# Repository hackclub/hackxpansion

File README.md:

<h1 align="center">
    Hackxpansion
</h1>

<h3 align="center">
    <a href="https://hackxpansion.koeg.dev">Website</a>
    <br/>
</h3>

<h4 align="center">
    A handheld console with 4 expansion solts
</h4>

<div align="center">
    
</div>

## Key Features

- Resistor based module identification at start up
- [2" 240x320 ST7789 LCD panel](https://www.buydisplay.com/2-inch-ips-tft-lcd-display-ips-panel-screen-240x320-for-smart-watch)
- RP2354 MCU
- Easily adaptable [module standard](https://hackxpansion.dino.icu/docs/detailed/card)
- Rust firmware with [embassy](https://embassy.dev/) and [slint-ui](https://slint.dev/)

## Why?

I really like the idea of modules, and modular things, and making people work together, so I made this.

## PCB

The console has two 4 layer PCBs designed in KiCAD, a main-board and a daughter-board, designed for JLC's basic process. 

### Main-Board

### Daughter-Board

## Making Your Own Modules

There are three simple steps to making your own module:

1. Design the module PCB in KiCAD
2. Design the module case in CAD
3. Write a driver for the module

There are detailed docs on the [hackxpansion website](https://hackxpansion.dino.icu/docs)

## Case

The case is designed in Autodesk Fusion, there are .f3z files in the hardware directory.

The models have parameters that can be adjusted to fit your needs.

## Shoutouts

Thank you so much for [Simon](https://github.com/NEOgHacking) who helped with the fanout of the RP, and also gave a ton of constructive feedback!!!!

## Zine

## BOM for Console

This is for an order of 2 PCBA PCBs.

Also found in a [CSV file](hardware/hackxpansion/BOM.csv). Each component has an LCSC part number attached that can be used to find the component on the LCSC website.

|Item                      |Price per unit|Nr of units|Total price|Link                                                                                          |
|--------------------------|--------------|-----------|-----------|----------------------------------------------------------------------------------------------|
|PCB with PCBA             |$60.00        |1          |$60.00     |https://jlcpcb.com/                                                                           |
|Display                   |$4.36         |1          |$4.36      |https://www.buydisplay.com/2-inch-ips-tft-lcd-display-ips-panel-screen-240x320-for-smart-watch|
|2x7 2.54mm header         |$0.386        |10         |$3.860     |https://www.aliexpress.com/item/1005012166781874.html                                         |
|Battery 502035            |$6.64         |1          |$6.64      |https://www.aliexpress.com/item/1005008218024646.html                                         |
|M2 OD3 L2 heat set insert |$0.0696       |15         |$1.0440    |https://www.aliexpress.com/item/1005006798286851.html                                         |
|M2 L6 screw               |$0.0766       |5          |$0.3830    |https://www.aliexpress.com/item/4000970993800.html                                            |
|M2 L8 screw               |$0.0766       |2          |$0.1532    |https://www.aliexpress.com/item/4000970993800.html                                            |
|M2 L4 screw               |$0.0766       |8          |$0.6128    |https://www.aliexpress.com/item/4000970993800.html                                            |
|                          |              |Total:     |$77.05     |                                                                                              |

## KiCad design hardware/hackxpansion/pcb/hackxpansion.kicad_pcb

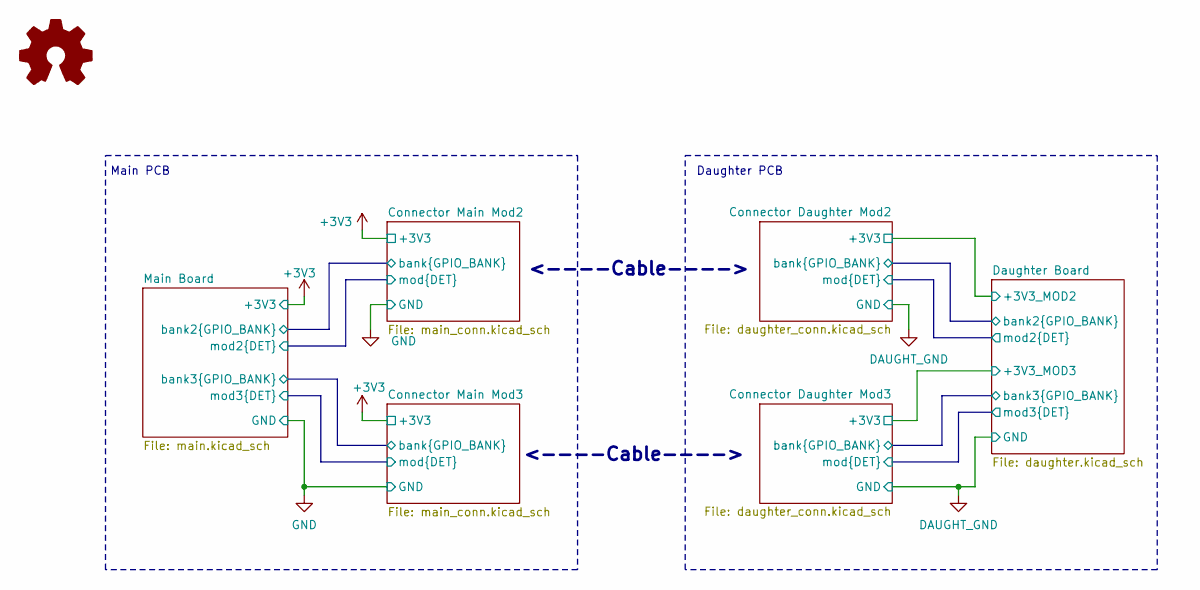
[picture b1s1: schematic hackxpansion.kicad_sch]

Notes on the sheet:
<----Cable---->
Main PCB
Daughter PCB

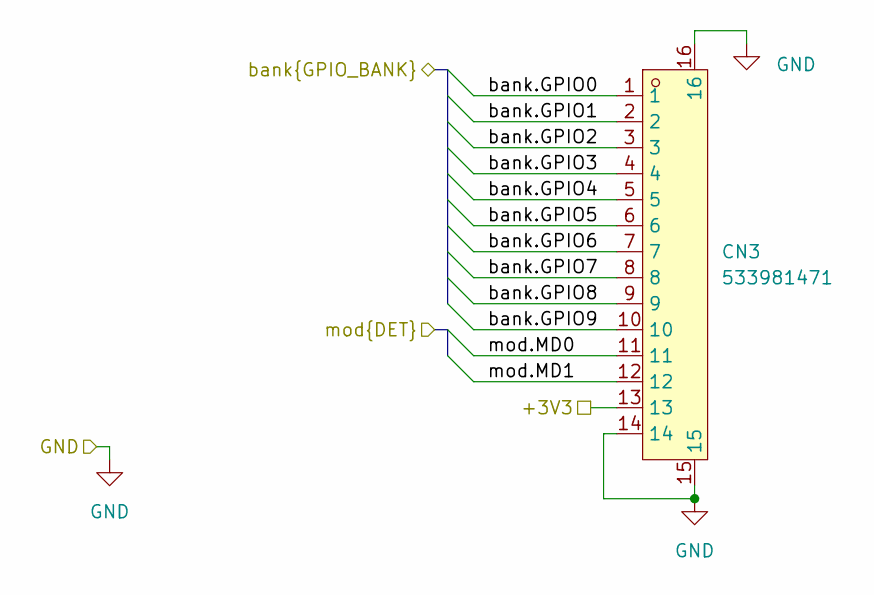
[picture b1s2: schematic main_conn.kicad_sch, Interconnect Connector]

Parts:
CN3: 533981471; CONN-SMD_14P-P1.25_MOLEX_533981471; MPN 533981471; LCSC C2886291

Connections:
/+3V3: CN3.13; also elsewhere on the board
/Connector Main Mod2/bank.GPIO0: CN3.1; also elsewhere on the board
/Connector Main Mod2/bank.GPIO1: CN3.2; also elsewhere on the board
/Connector Main Mod2/bank.GPIO2: CN3.3; also elsewhere on the board
/Connector Main Mod2/bank.GPIO3: CN3.4; also elsewhere on the board
/Connector Main Mod2/bank.GPIO4: CN3.5; also elsewhere on the board
/Connector Main Mod2/bank.GPIO5: CN3.6; also elsewhere on the board
/Connector Main Mod2/bank.GPIO6: CN3.7; also elsewhere on the board
/Connector Main Mod2/bank.GPIO7: CN3.8; also elsewhere on the board
/Connector Main Mod2/bank.GPIO8: CN3.9; also elsewhere on the board
/Connector Main Mod2/bank.GPIO9: CN3.10; also elsewhere on the board
/Connector Main Mod2/mod.MD0: CN3.11; also elsewhere on the board
/Connector Main Mod2/mod.MD1: CN3.12; also elsewhere on the board
/GND: CN3.14, CN3.15, CN3.16; also elsewhere on the board

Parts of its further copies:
CN2: 533981471; CONN-SMD_14P-P1.25_MOLEX_533981471; MPN 533981471; LCSC C2886291

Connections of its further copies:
/+3V3: CN2.13; also elsewhere on the board
/Connector Main Mod3/bank.GPIO0: CN2.1; also elsewhere on the board
/Connector Main Mod3/bank.GPIO1: CN2.2; also elsewhere on the board
/Connector Main Mod3/bank.GPIO2: CN2.3; also elsewhere on the board
/Connector Main Mod3/bank.GPIO3: CN2.4; also elsewhere on the board
/Connector Main Mod3/bank.GPIO4: CN2.5; also elsewhere on the board
/Connector Main Mod3/bank.GPIO5: CN2.6; also elsewhere on the board
/Connector Main Mod3/bank.GPIO6: CN2.7; also elsewhere on the board
/Connector Main Mod3/bank.GPIO7: CN2.8; also elsewhere on the board
/Connector Main Mod3/bank.GPIO8: CN2.9; also elsewhere on the board
/Connector Main Mod3/bank.GPIO9: CN2.10; also elsewhere on the board
/Connector Main Mod3/mod.MD0: CN2.11; also elsewhere on the board
/Connector Main Mod3/mod.MD1: CN2.12; also elsewhere on the board
/GND: CN2.14, CN2.15, CN2.16; also elsewhere on the board

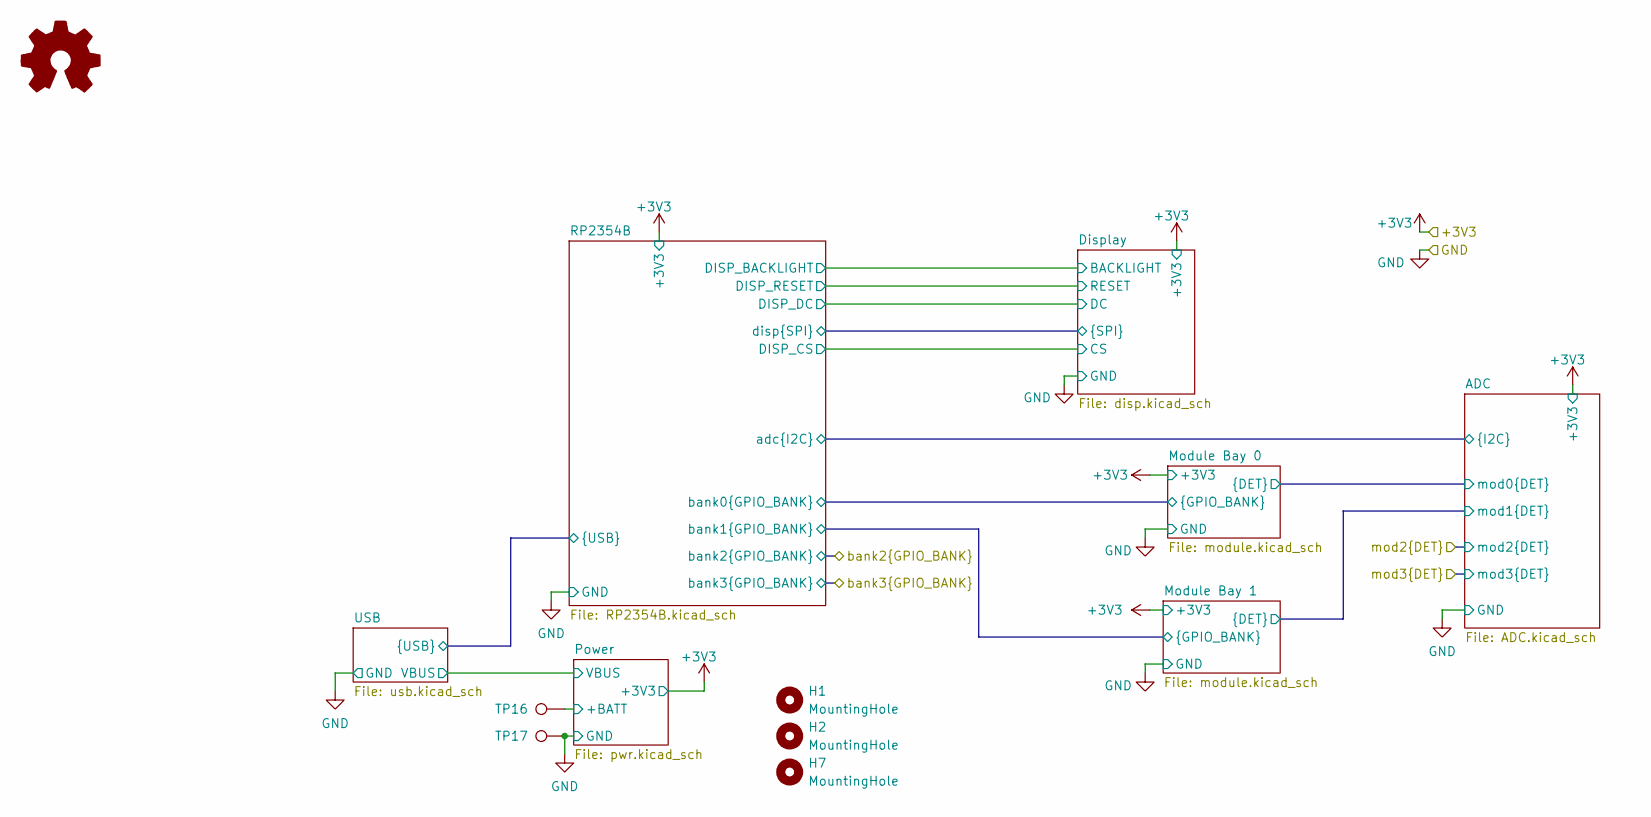
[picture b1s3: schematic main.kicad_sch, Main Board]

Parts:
H1, H2, H7: MountingHole; MountingHole_2.2mm_M2
SYM1: Logo_Open_Hardware_Small; OSHW-Logo2_14.6x12mm_SilkScreen
TP16: BATT+; TestPoint_Pad_D1.5mm
TP17: BATT-; TestPoint_Pad_D1.5mm

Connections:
/GND: TP17.1 (1_1); also elsewhere on the board
/Main Board/Power/+BATT: TP16.1 (1_1); also elsewhere on the board

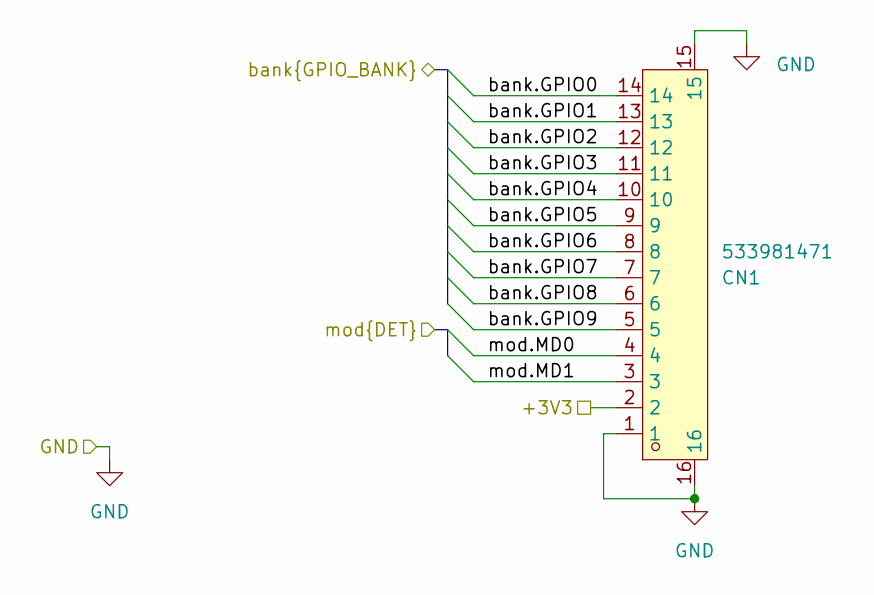
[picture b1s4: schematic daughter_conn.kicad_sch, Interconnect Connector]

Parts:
CN1: 533981471; CONN-SMD_14P-P1.25_MOLEX_533981471; MPN 533981471; LCSC C2886291

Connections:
/Connector Daughter Mod2/bank.GPIO0: CN1.14; also elsewhere on the board
/Connector Daughter Mod2/bank.GPIO1: CN1.13; also elsewhere on the board
/Connector Daughter Mod2/bank.GPIO2: CN1.12; also elsewhere on the board
/Connector Daughter Mod2/bank.GPIO3: CN1.11; also elsewhere on the board
/Connector Daughter Mod2/bank.GPIO4: CN1.10; also elsewhere on the board
/Connector Daughter Mod2/bank.GPIO5: CN1.9; also elsewhere on the board
/Connector Daughter Mod2/bank.GPIO6: CN1.8; also elsewhere on the board
/Connector Daughter Mod2/bank.GPIO7: CN1.7; also elsewhere on the board
/Connector Daughter Mod2/bank.GPIO8: CN1.6; also elsewhere on the board
/Connector Daughter Mod2/bank.GPIO9: CN1.5; also elsewhere on the board
/Connector Daughter Mod2/mod.MD0: CN1.4; also elsewhere on the board
/Connector Daughter Mod2/mod.MD1: CN1.3; also elsewhere on the board
/DAUGHT_GND: CN1.1, CN1.15, CN1.16; also elsewhere on the board
/Daughter Board/+3V3_MOD2: CN1.2; also elsewhere on the board

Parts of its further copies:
CN4: 533981471; CONN-SMD_14P-P1.25_MOLEX_533981471; MPN 533981471; LCSC C2886291

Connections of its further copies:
/Connector Daughter Mod3/bank.GPIO0: CN4.14; also elsewhere on the board
/Connector Daughter Mod3/bank.GPIO1: CN4.13; also elsewhere on the board
/Connector Daughter Mod3/bank.GPIO2: CN4.12; also elsewhere on the board
/Connector Daughter Mod3/bank.GPIO3: CN4.11; also elsewhere on the board
/Connector Daughter Mod3/bank.GPIO4: CN4.10; also elsewhere on the board
/Connector Daughter Mod3/bank.GPIO5: CN4.9; also elsewhere on the board
/Connector Daughter Mod3/bank.GPIO6: CN4.8; also elsewhere on the board
/Connector Daughter Mod3/bank.GPIO7: CN4.7; also elsewhere on the board
/Connector Daughter Mod3/bank.GPIO8: CN4.6; also elsewhere on the board
/Connector Daughter Mod3/bank.GPIO9: CN4.5; also elsewhere on the board
/Connector Daughter Mod3/mod.MD0: CN4.4; also elsewhere on the board
/Connector Daughter Mod3/mod.MD1: CN4.3; also elsewhere on the board
/DAUGHT_GND: CN4.1, CN4.15, CN4.16; also elsewhere on the board
/Daughter Board/+3V3_MOD3: CN4.2; also elsewhere on the board

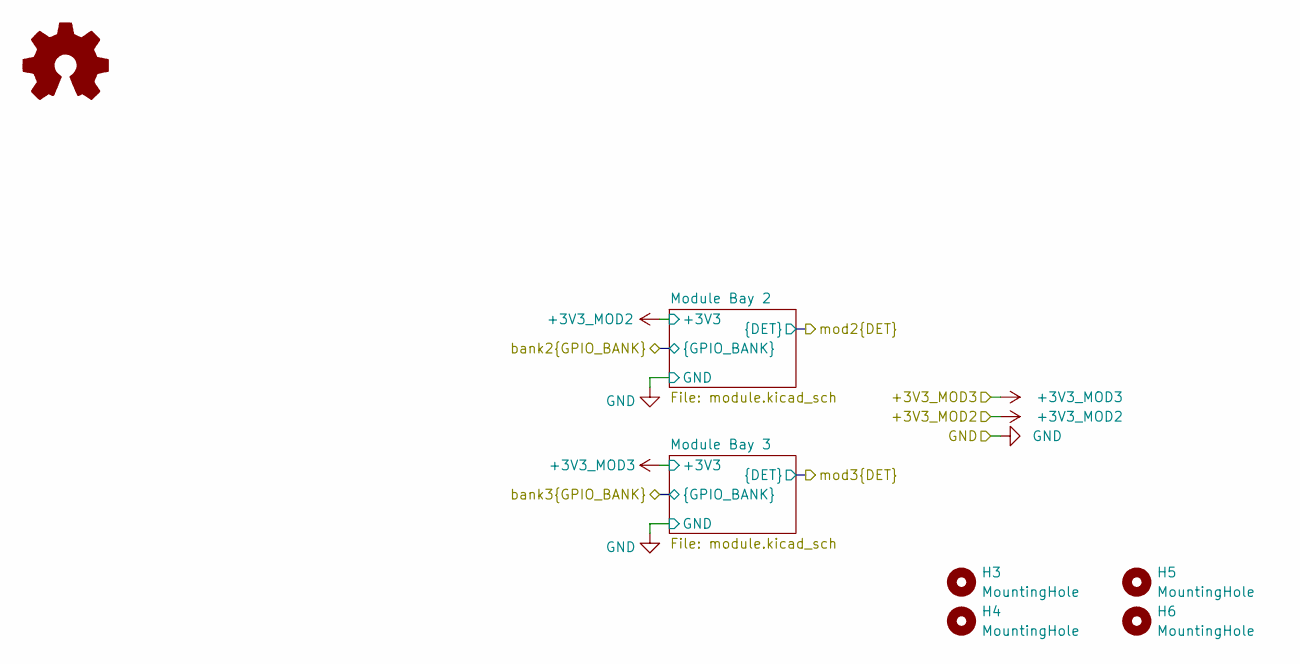
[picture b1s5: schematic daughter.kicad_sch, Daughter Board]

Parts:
H3, H4, H5, H6: MountingHole; MountingHole_2.2mm_M2
SYM2: Logo_Open_Hardware_Small; OSHW-Logo_5.7x6mm_SilkScreen

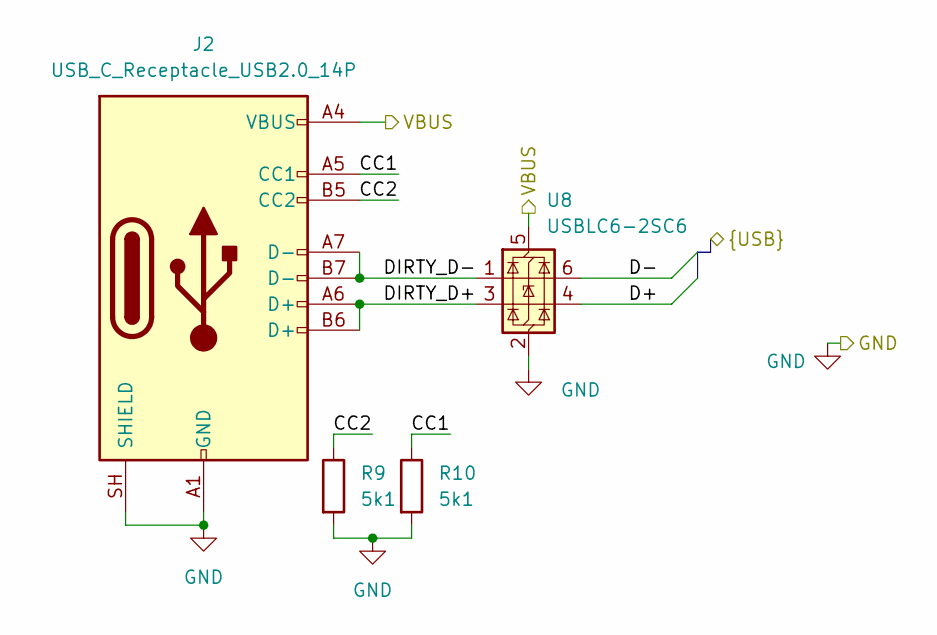
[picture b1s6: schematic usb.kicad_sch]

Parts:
J2: USB_C_Receptacle_USB2.0_14P; USB-C-SMD_TYPE-C-16PIN-2MD-073; LCSC C2765186
R9, R10: 5k1; R_0402_1005Metric; LCSC C25905
U8: USBLC6-2SC6; SOT-23-6; LCSC C2827654

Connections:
/GND: J2.A1 (GND), J2.A12 (GND), J2.B1 (GND), J2.B12 (GND), J2.SH (SHIELD), R9.2, R10.2, U8.2 (GND); also elsewhere on the board
/Main Board/Power/VBUS: J2.A4 (VBUS), J2.A9 (VBUS), J2.B4 (VBUS), J2.B9 (VBUS), U8.5 (VBUS); also elsewhere on the board
/Main Board/RP2354B/D+: U8.4 (I/O2); also elsewhere on the board
/Main Board/RP2354B/D-: U8.6 (I/O1); also elsewhere on the board
/Main Board/USB/CC1: J2.A5 (CC1), R10.1
/Main Board/USB/CC2: J2.B5 (CC2), R9.1
/Main Board/USB/DIRTY_D+: J2.A6 (D+), J2.B6 (D+), U8.3 (I/O2)
/Main Board/USB/DIRTY_D-: J2.A7 (D-), J2.B7 (D-), U8.1 (I/O1)

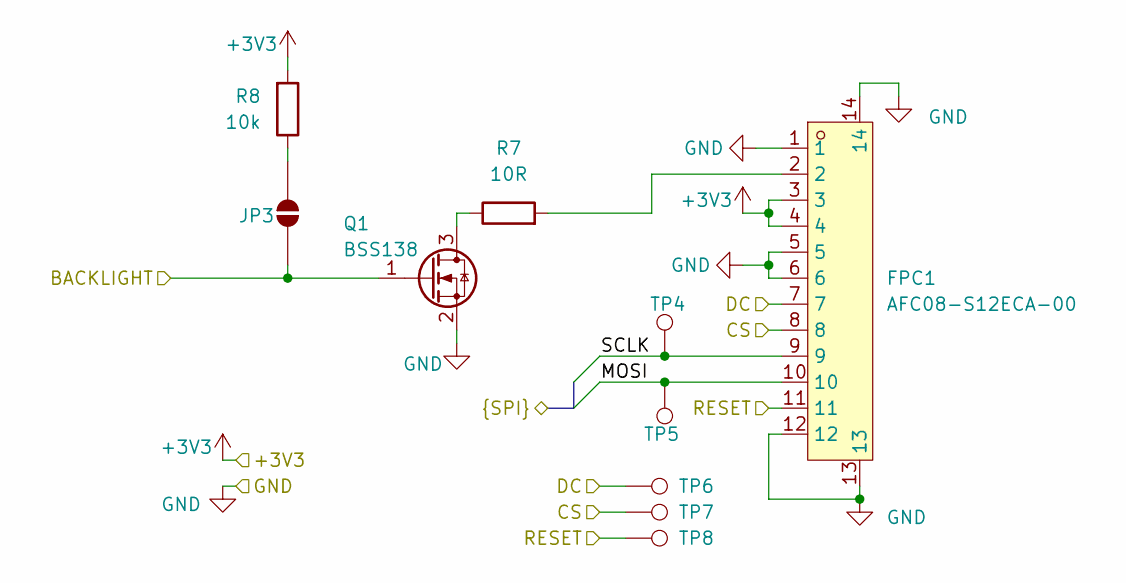
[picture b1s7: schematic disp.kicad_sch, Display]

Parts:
FPC1: AFC08-S12ECA-00; FPC-SMD_P0.80-12P_LCS-SJ-H2.0; MPN AFC08-S12ECA-00; LCSC C262331
JP3: SolderJumper_2_Open; SolderJumper-2_P1.3mm_Open_RoundedPad1.0x1.5mm
Q1: BSS138; SOT-23; LCSC C78284
R7: 10R; R_0402_1005Metric; LCSC C25077
R8: 10k; R_0402_1005Metric; LCSC C190095
TP4, TP5, TP6, TP7, TP8: TestPoint; TestPoint_Pad_D1.0mm

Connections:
/+3V3: FPC1.3, FPC1.4, R8.2; also elsewhere on the board
/GND: FPC1.1, FPC1.5, FPC1.6, FPC1.12, FPC1.13, FPC1.14, Q1.2 (S); also elsewhere on the board
/Main Board/Display/BACKLIGHT: JP3.2 (B), Q1.1 (G); also elsewhere on the board
/Main Board/Display/CS: FPC1.8, TP7.1 (1_1); also elsewhere on the board
/Main Board/Display/DC: FPC1.7, TP6.1 (1_1); also elsewhere on the board
/Main Board/Display/MOSI: FPC1.10, TP5.1 (1_1); also elsewhere on the board
/Main Board/Display/RESET: FPC1.11, TP8.1 (1_1); also elsewhere on the board
/Main Board/Display/SCLK: FPC1.9, TP4.1 (1_1); also elsewhere on the board
unnamed: FPC1.2, R7.2
unnamed: JP3.1 (A), R8.1
unnamed: Q1.3 (D), R7.1

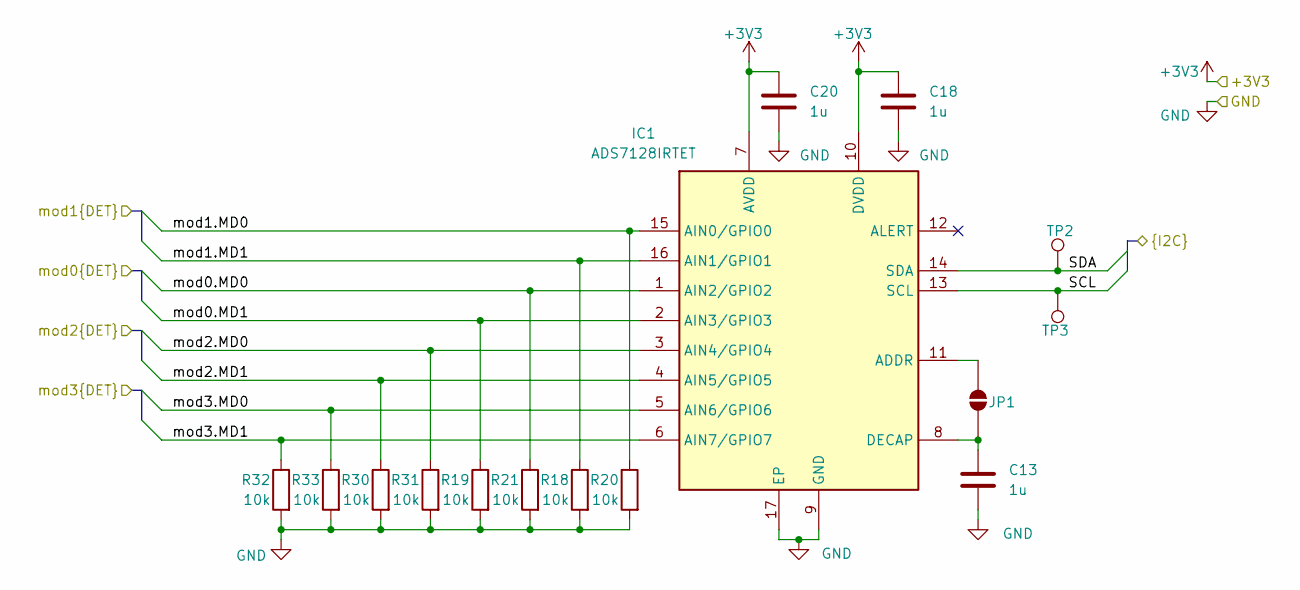
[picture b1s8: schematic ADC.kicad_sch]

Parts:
C13, C18, C20: 1u; C_0402_1005Metric; LCSC C52923
IC1: ADS7128IRTET; QFN50P300X300X80-17N-D; Manufacturer_Part_Number ADS7128IRTET; Mouser Part Number 595-ADS7128IRTET
JP1: SolderJumper_2_Open; SolderJumper-2_P1.3mm_Open_RoundedPad1.0x1.5mm
R18, R19, R20, R21, R30, R31, R32, R33: 10k; R_0402_1005Metric; LCSC C190095
TP2, TP3: TestPoint; TestPoint_Pad_D1.0mm

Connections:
/+3V3: C18.1, C20.1, IC1.7 (AVDD), IC1.10 (DVDD); also elsewhere on the board
/Connector Main Mod2/mod.MD0: IC1.3 (AIN4/GPIO4), R31.1; also elsewhere on the board
/Connector Main Mod2/mod.MD1: IC1.4 (AIN5/GPIO5), R30.1; also elsewhere on the board
/Connector Main Mod3/mod.MD0: IC1.5 (AIN6/GPIO6), R33.1; also elsewhere on the board
/Connector Main Mod3/mod.MD1: IC1.6 (AIN7/GPIO7), R32.1; also elsewhere on the board
/GND: C13.2, C18.2, C20.2, IC1.9 (GND), IC1.17 (EP), R18.2, R19.2, R20.2, R21.2, R30.2, R31.2, R32.2, R33.2; also elsewhere on the board
/Main Board/ADC/SCL: IC1.13 (SCL), TP3.1 (1_1); also elsewhere on the board
/Main Board/ADC/SDA: IC1.14 (SDA), TP2.1 (1_1); also elsewhere on the board
/Main Board/ADC/mod0.MD0: IC1.1 (AIN2/GPIO2), R21.1; also elsewhere on the board
/Main Board/ADC/mod0.MD1: IC1.2 (AIN3/GPIO3), R19.1; also elsewhere on the board
/Main Board/ADC/mod1.MD0: IC1.15 (AIN0/GPIO0), R20.1; also elsewhere on the board
/Main Board/ADC/mod1.MD1: IC1.16 (AIN1/GPIO1), R18.1; also elsewhere on the board
unnamed: IC1.11 (ADDR), JP1.1 (A)
unnamed: C13.1, IC1.8 (DECAP), JP1.2 (B)

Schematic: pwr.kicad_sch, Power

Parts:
C21, C22, C23, C24: 4u7; C_0402_1005Metric; LCSC C23733
D1: LED; LED_0603_1608Metric; LCSC C965808
Q2: 2N7002; SOT-23; LCSC C8545
R13: 100R; R_0402_1005Metric; LCSC C25076
R14, R15, R24: 10k; R_0402_1005Metric; LCSC C190095
R22: 3k3; R_0402_1005Metric; LCSC C25890
R23, R25: 1k5; R_0402_1005Metric; LCSC C25867
SW3: SW_On_Off; SW_CK_JS202011AQN_DPDT_Angled; LCSC C221662
TP9, TP10: TestPoint; TestPoint_Pad_D1.0mm
U5: SPX3819M5-L-3-3; SOT-23-5; LCSC C20617301
U7: BQ24075RGT; VQFN-16-1EP_3x3mm_P0.5mm_EP1.6x1.6mm; LCSC C2865459

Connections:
/+3V3: C24.2, D1.2 (A), TP10.1 (1_1), U5.5 (OUT); also elsewhere on the board
/GND: C21.1, C22.1, C23.1, C24.1, Q2.2 (S), R14.2, R22.2, R23.2, R24.2, SW3.1 (A), U5.2 (GND), U7.4 (~CE), U7.5 (EN2), U7.8 (VSS), U7.17 (VSS); also elsewhere on the board
/Main Board/Power/+BATT: C22.2, R15.1, U7.2 (BAT), U7.3 (BAT); also elsewhere on the board
/Main Board/Power/ILIM: R23.1, U7.12 (ILIM)
/Main Board/Power/ISET: R22.1, U7.16 (ISET)
/Main Board/Power/REG-OUT: C23.2, TP9.1 (1_1), U5.1 (IN), U5.3 (EN), U7.6 (EN1), U7.10 (OUT), U7.11 (OUT)
/Main Board/Power/SYSOFF: Q2.3 (D), SW3.2 (B), U7.15 (SYSOFF)
/Main Board/Power/TS: R24.1, U7.1 (TS)
/Main Board/Power/VBUS: C21.2, R13.1, U7.13 (IN); also elsewhere on the board
unnamed: D1.1 (K), R25.1
unnamed: Q2.1 (G), R13.2, R14.1
unnamed: R15.2, SW3.3 (C)
unnamed: R25.2, U7.9 (~CHG)

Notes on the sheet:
On/Off Switch

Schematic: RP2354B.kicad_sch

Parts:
C1, C3, C4, C5, C6, C7, C8, C9, C10, C11, C12: 100n; C_0402_1005Metric; LCSC C1525
C2, C14: 4u7; C_0402_1005Metric; LCSC C23733
C15, C16: 4u7; C_0402_1005Metric_small_pads; LCSC C23733
C17, C19: 15p; C_0402_1005Metric; LCSC C1548
J3: Conn_ARM_JTAG_SWD_10; PinHeader_2x05_P1.27mm_Vertical_SMD; LCSC C2935458
L1: 3u3; L_pol_2016; LCSC C42411119
R1, R3, R6: 1k; R_0402_1005Metric; LCSC C11702
R2: 33R; R_0402_1005Metric; LCSC C25105
R4, R5: 27R; R_0402_1005Metric; LCSC C2929914
R11, R12: 10k; R_0402_1005Metric; LCSC C190095
SW1, SW2: SW_Push; SW_SPST_B3U-1000P; LCSC C231329
TP11, TP12, TP13, TP14, TP15: TestPoint; TestPoint_Pad_D1.0mm
U2: RP2354B; RP2350-QFN-80-1EP_10x10_P0.4mm_EP3.4x3.4mm_ThermalVias; LCSC C39843328
Y1: ABM8-272-T3; Crystal_SMD_3225-4Pin_3.2x2.5mm; LCSC C20625731

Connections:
+1V1: C1.1, C2.1, C3.1, C16.1, L1.1, U2.10 (DVDD), U2.32 (DVDD), U2.51 (DVDD), U2.65 (VREG_FB)
/+3V3: C4.1, C5.1, C6.1, C7.1, C8.1, C9.1, C10.1, C11.1, C12.1, C15.1, J3.1 (VTref), R2.1, R11.2, R12.2, U2.5 (IOVDD), U2.15 (IOVDD), U2.24 (IOVDD), U2.29 (IOVDD), U2.41 (IOVDD), U2.50 (IOVDD), U2.59 (ADC_AVDD), U2.60 (IOVDD), U2.64 (VREG_VIN), U2.68 (USB_OTP_VDD), U2.69 (QSPI_IOVDD), U2.76 (IOVDD); also elsewhere on the board
/Connector Main Mod2/bank.GPIO0: U2.4 (GPIO7); also elsewhere on the board
/Connector Main Mod2/bank.GPIO1: U2.3 (GPIO6); also elsewhere on the board
/Connector Main Mod2/bank.GPIO2: U2.79 (GPIO2); also elsewhere on the board
/Connector Main Mod2/bank.GPIO3: U2.1 (GPIO4); also elsewhere on the board
/Connector Main Mod2/bank.GPIO4: U2.80 (GPIO3); also elsewhere on the board
/Connector Main Mod2/bank.GPIO5: U2.77 (GPIO0); also elsewhere on the board
/Connector Main Mod2/bank.GPIO6: U2.78 (GPIO1); also elsewhere on the board
/Connector Main Mod2/bank.GPIO7: U2.49 (GPIO40/ADC0); also elsewhere on the board
/Connector Main Mod2/bank.GPIO8: U2.52 (GPIO41/ADC1); also elsewhere on the board
/Connector Main Mod2/bank.GPIO9: U2.42 (GPIO33); also elsewhere on the board
/Connector Main Mod3/bank.GPIO0: U2.12 (GPIO13); also elsewhere on the board
/Connector Main Mod3/bank.GPIO1: U2.16 (GPIO16); also elsewhere on the board
/Connector Main Mod3/bank.GPIO2: U2.8 (GPIO10); also elsewhere on the board
/Connector Main Mod3/bank.GPIO3: U2.11 (GPIO12); also elsewhere on the board
/Connector Main Mod3/bank.GPIO4: U2.9 (GPIO11); also elsewhere on the board
/Connector Main Mod3/bank.GPIO5: U2.20 (GPIO20); also elsewhere on the board
/Connector Main Mod3/bank.GPIO6: U2.21 (GPIO21); also elsewhere on the board
/Connector Main Mod3/bank.GPIO7: U2.53 (GPIO42/ADC2); also elsewhere on the board
/Connector Main Mod3/bank.GPIO8: U2.54 (GPIO43/ADC3); also elsewhere on the board
/Connector Main Mod3/bank.GPIO9: U2.17 (GPIO17); also elsewhere on the board
/GND: C1.2, C2.2, C3.2, C4.2, C5.2, C6.2, C7.2, C8.2, C9.2, C10.2, C11.2, C12.2, C14.2, C15.2, C16.2, C17.1, C19.1, J3.3 (GND), J3.5 (GND), J3.9 (GNDDetect), SW1.1, SW2.1, U2.62 (VREG_PGND), U2.81 (GND), Y1.2 (G), Y1.4 (G); also elsewhere on the board
/Main Board/ADC/SCL: R12.1, U2.14 (GPIO15); also elsewhere on the board
/Main Board/ADC/SDA: R11.1, U2.13 (GPIO14); also elsewhere on the board
/Main Board/Display/BACKLIGHT: U2.39 (GPIO31); also elsewhere on the board
/Main Board/Display/CS: U2.47 (GPIO38); also elsewhere on the board
/Main Board/Display/DC: U2.26 (GPIO25); also elsewhere on the board
/Main Board/Display/MOSI: U2.44 (GPIO35); also elsewhere on the board
/Main Board/Display/RESET: U2.2 (GPIO5); also elsewhere on the board
/Main Board/Display/SCLK: U2.43 (GPIO34); also elsewhere on the board
/Main Board/Module Bay 0/GPIO0: U2.46 (GPIO37); also elsewhere on the board
/Main Board/Module Bay 0/GPIO1: U2.45 (GPIO36); also elsewhere on the board
/Main Board/Module Bay 0/GPIO2: U2.38 (GPIO30); also elsewhere on the board
/Main Board/Module Bay 0/GPIO3: U2.25 (GPIO24); also elsewhere on the board
/Main Board/Module Bay 0/GPIO4: U2.28 (GPIO27); also elsewhere on the board
/Main Board/Module Bay 0/GPIO5: U2.6 (GPIO8); also elsewhere on the board
/Main Board/Module Bay 0/GPIO6: U2.7 (GPIO9); also elsewhere on the board
/Main Board/Module Bay 0/GPIO7: U2.57 (GPIO46/ADC6); also elsewhere on the board
/Main Board/Module Bay 0/GPIO8: U2.58 (GPIO47/ADC7); also elsewhere on the board
/Main Board/Module Bay 0/GPIO9: U2.48 (GPIO39); also elsewhere on the board
/Main Board/Module Bay 1/GPIO0: U2.19 (GPIO19); also elsewhere on the board
/Main Board/Module Bay 1/GPIO1: U2.18 (GPIO18); also elsewhere on the board
/Main Board/Module Bay 1/GPIO2: U2.22 (GPIO22); also elsewhere on the board
/Main Board/Module Bay 1/GPIO3: U2.40 (GPIO32); also elsewhere on the board
/Main Board/Module Bay 1/GPIO4: U2.23 (GPIO23); also elsewhere on the board
/Main Board/Module Bay 1/GPIO5: U2.36 (GPIO28); also elsewhere on the board
/Main Board/Module Bay 1/GPIO6: U2.37 (GPIO29); also elsewhere on the board
/Main Board/Module Bay 1/GPIO7: U2.55 (GPIO44/ADC4); also elsewhere on the board
/Main Board/Module Bay 1/GPIO8: U2.56 (GPIO45/ADC5); also elsewhere on the board
/Main Board/Module Bay 1/GPIO9: U2.27 (GPIO26); also elsewhere on the board
/Main Board/RP2354B/D+: R5.1; also elsewhere on the board
/Main Board/RP2354B/D-: R4.1; also elsewhere on the board
/Main Board/RP2354B/QSPI_SS: R1.2, U2.75 (~QSPI_SS)
/Main Board/RP2354B/RUN: J3.10 (~RESET), R3.2, U2.35 (RUN)
/Main Board/RP2354B/SWCLK: J3.4 (SWCLK/TCK), U2.33 (SWCLK)
/Main Board/RP2354B/SWDIO: J3.2 (SWDIO/TMS), U2.34 (SWDIO)
/Main Board/RP2354B/~USB_BOOT: R1.1, SW1.2
unnamed: C19.2, R6.1, Y1.3
unnamed: R3.1, SW2.2
unnamed: TP11.1 (1_1), U2.71 (QSPI_SCLK)
unnamed: TP15.1 (1_1), U2.72 (QSPI_SD0)
unnamed: TP12.1 (1_1), U2.74 (QSPI_SD1)
unnamed: TP13.1 (1_1), U2.73 (QSPI_SD2)
unnamed: TP14.1 (1_1), U2.70 (QSPI_SD3)
unnamed: R4.2, U2.66 (USB_DM)
unnamed: R5.2, U2.67 (USB_DP)
unnamed: C14.1, R2.2, U2.61 (VREG_AVDD)
unnamed: L1.2, U2.63 (VREG_LX)
unnamed: C17.2, U2.30 (XIN), Y1.1
unnamed: R6.2, U2.31 (XOUT)

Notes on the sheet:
i2c0, spi1, uart1
i2c1, spi0, uart0
Buttons
SWD Connector

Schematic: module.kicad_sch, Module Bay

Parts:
U1: PinSocket_2x07_P2.54mm_Horizontal

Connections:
/+3V3: U1.2 (3V3); also elsewhere on the board
/GND: U1.1 (GND); also elsewhere on the board
/Main Board/ADC/mod0.MD0: U1.3 (MD0); also elsewhere on the board
/Main Board/ADC/mod0.MD1: U1.4 (MD1); also elsewhere on the board
/Main Board/Module Bay 0/GPIO0: U1.5 (GPIO0); also elsewhere on the board
/Main Board/Module Bay 0/GPIO1: U1.6 (GPIO1); also elsewhere on the board
/Main Board/Module Bay 0/GPIO2: U1.7 (GPI02); also elsewhere on the board
/Main Board/Module Bay 0/GPIO3: U1.8 (GPIO3); also elsewhere on the board
/Main Board/Module Bay 0/GPIO4: U1.9 (GPIO4); also elsewhere on the board
/Main Board/Module Bay 0/GPIO5: U1.10 (GPIO5); also elsewhere on the board
/Main Board/Module Bay 0/GPIO6: U1.11 (GPIO6); also elsewhere on the board
/Main Board/Module Bay 0/GPIO7: U1.12 (GPIO7); also elsewhere on the board
/Main Board/Module Bay 0/GPIO8: U1.13 (GPIO8); also elsewhere on the board
/Main Board/Module Bay 0/GPIO9: U1.14 (GPIO9); also elsewhere on the board

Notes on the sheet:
E24 for the module detect resistors 1k->10k, 10k->100k 0.1%

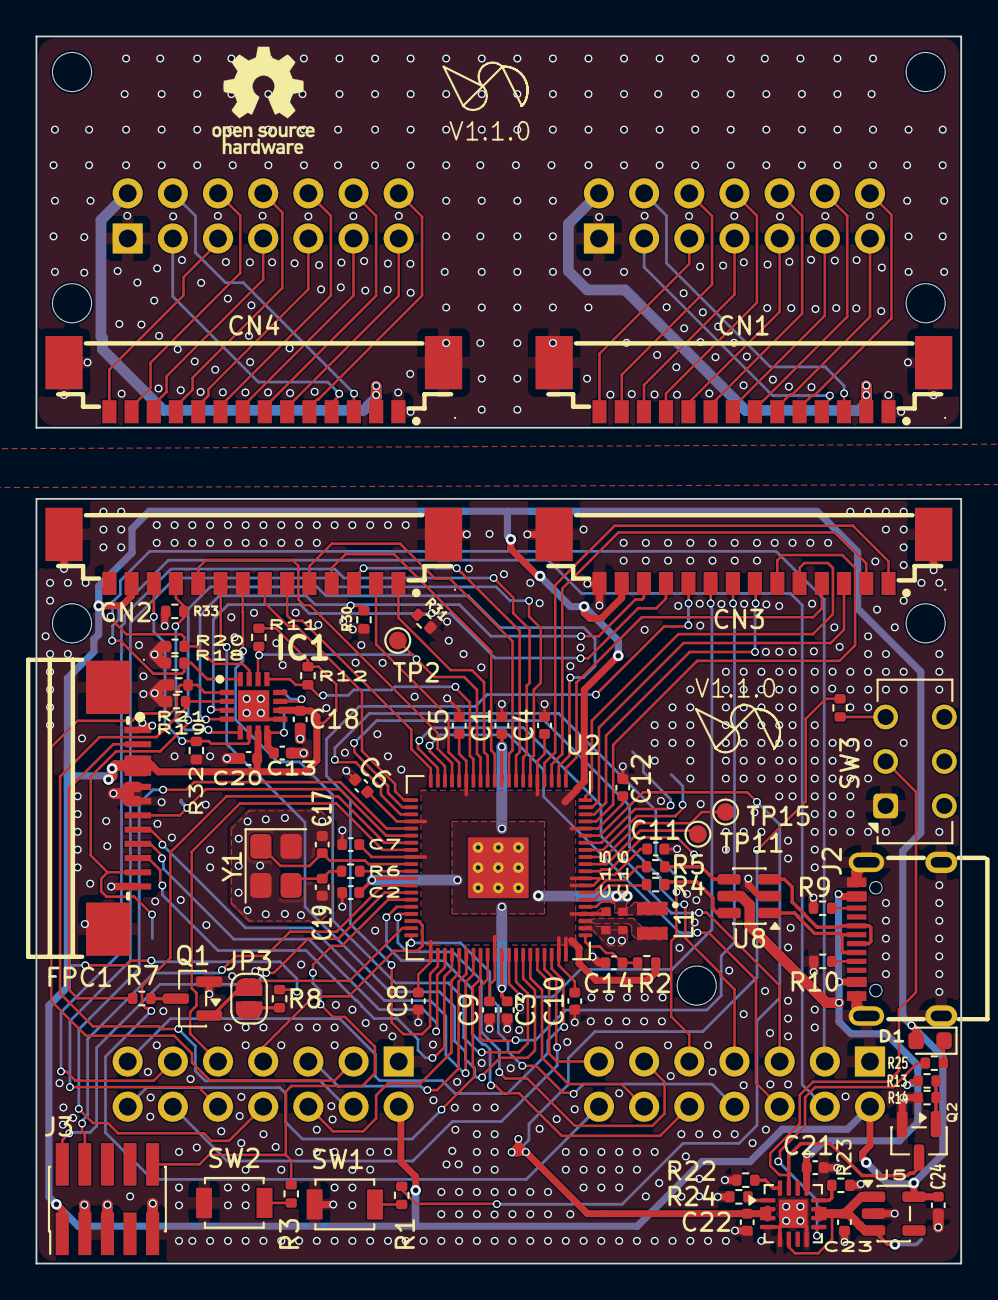
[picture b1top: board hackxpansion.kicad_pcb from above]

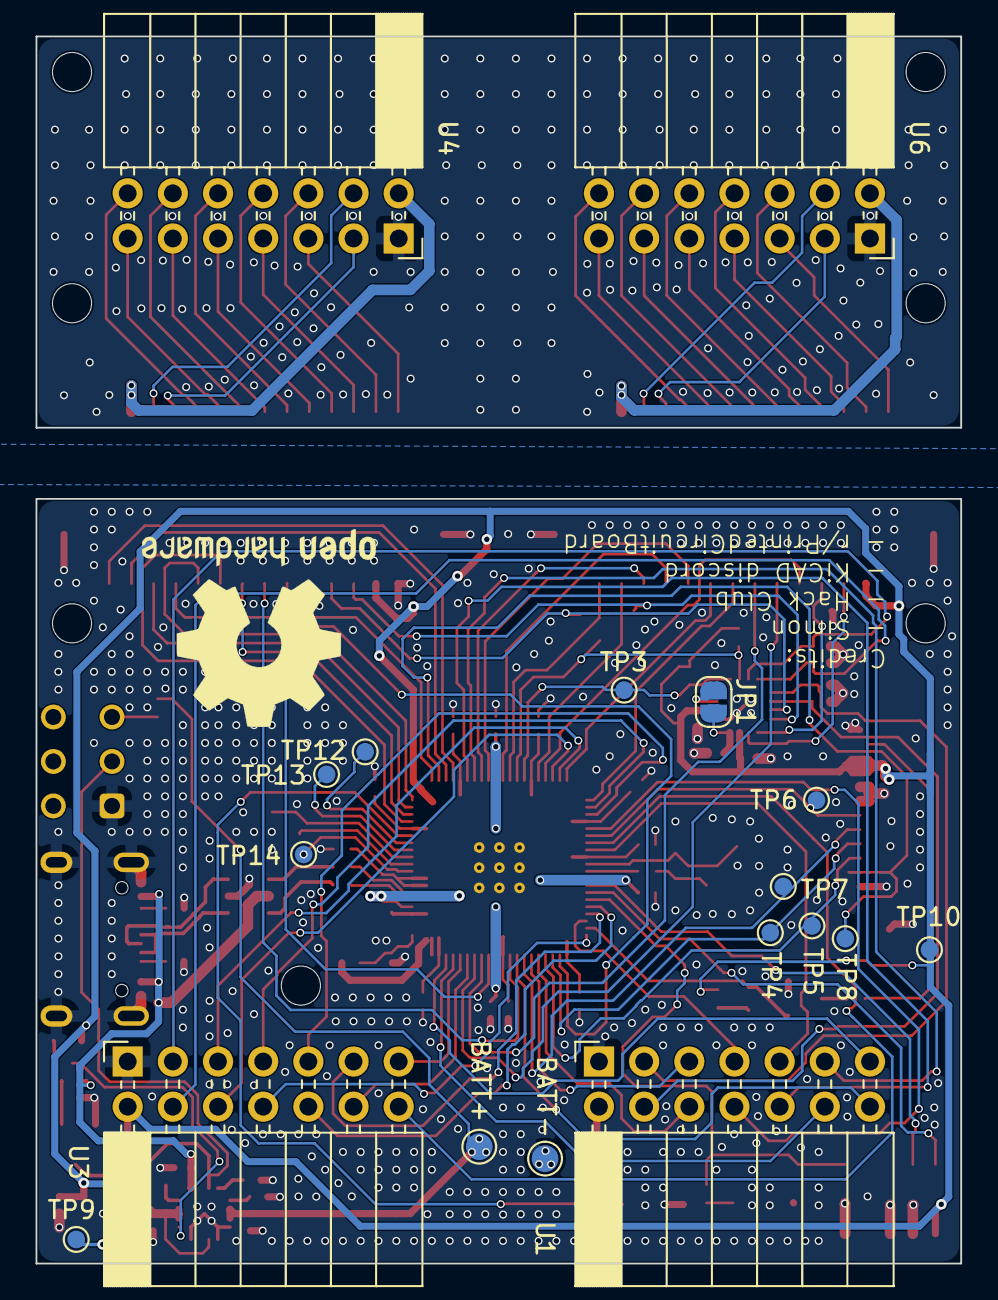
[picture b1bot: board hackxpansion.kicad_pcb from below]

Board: 4 copper layers, 52.0 x 43.0 mm, 102 parts (22 on the bottom side), 126 nets.

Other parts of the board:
U3, U4, U6: PinSocket_2x07_P2.54mm_Horizontal

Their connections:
/+3V3: U3.2 (3V3); also elsewhere on the board
/Connector Daughter Mod2/bank.GPIO0: U4.5 (GPIO0); also elsewhere on the board
/Connector Daughter Mod2/bank.GPIO1: U4.6 (GPIO1); also elsewhere on the board
/Connector Daughter Mod2/bank.GPIO2: U4.7 (GPI02); also elsewhere on the board
/Connector Daughter Mod2/bank.GPIO3: U4.8 (GPIO3); also elsewhere on the board
/Connector Daughter Mod2/bank.GPIO4: U4.9 (GPIO4); also elsewhere on the board
/Connector Daughter Mod2/bank.GPIO5: U4.10 (GPIO5); also elsewhere on the board
/Connector Daughter Mod2/bank.GPIO6: U4.11 (GPIO6); also elsewhere on the board
/Connector Daughter Mod2/bank.GPIO7: U4.12 (GPIO7); also elsewhere on the board
/Connector Daughter Mod2/bank.GPIO8: U4.13 (GPIO8); also elsewhere on the board
/Connector Daughter Mod2/bank.GPIO9: U4.14 (GPIO9); also elsewhere on the board
/Connector Daughter Mod2/mod.MD0: U4.3 (MD0); also elsewhere on the board
/Connector Daughter Mod2/mod.MD1: U4.4 (MD1); also elsewhere on the board
/Connector Daughter Mod3/bank.GPIO0: U6.5 (GPIO0); also elsewhere on the board
/Connector Daughter Mod3/bank.GPIO1: U6.6 (GPIO1); also elsewhere on the board
/Connector Daughter Mod3/bank.GPIO2: U6.7 (GPI02); also elsewhere on the board
/Connector Daughter Mod3/bank.GPIO3: U6.8 (GPIO3); also elsewhere on the board
/Connector Daughter Mod3/bank.GPIO4: U6.9 (GPIO4); also elsewhere on the board
/Connector Daughter Mod3/bank.GPIO5: U6.10 (GPIO5); also elsewhere on the board
/Connector Daughter Mod3/bank.GPIO6: U6.11 (GPIO6); also elsewhere on the board
/Connector Daughter Mod3/bank.GPIO7: U6.12 (GPIO7); also elsewhere on the board
/Connector Daughter Mod3/bank.GPIO8: U6.13 (GPIO8); also elsewhere on the board
/Connector Daughter Mod3/bank.GPIO9: U6.14 (GPIO9); also elsewhere on the board
/Connector Daughter Mod3/mod.MD0: U6.3 (MD0); also elsewhere on the board
/Connector Daughter Mod3/mod.MD1: U6.4 (MD1); also elsewhere on the board
/DAUGHT_GND: U4.1 (GND), U6.1 (GND); also elsewhere on the board
/Daughter Board/+3V3_MOD2: U4.2 (3V3); also elsewhere on the board
/Daughter Board/+3V3_MOD3: U6.2 (3V3); also elsewhere on the board
/GND: U3.1 (GND); also elsewhere on the board
/Main Board/ADC/mod1.MD0: U3.3 (MD0); also elsewhere on the board
/Main Board/ADC/mod1.MD1: U3.4 (MD1); also elsewhere on the board
/Main Board/Module Bay 1/GPIO0: U3.5 (GPIO0); also elsewhere on the board
/Main Board/Module Bay 1/GPIO1: U3.6 (GPIO1); also elsewhere on the board
/Main Board/Module Bay 1/GPIO2: U3.7 (GPI02); also elsewhere on the board
/Main Board/Module Bay 1/GPIO3: U3.8 (GPIO3); also elsewhere on the board
/Main Board/Module Bay 1/GPIO4: U3.9 (GPIO4); also elsewhere on the board
/Main Board/Module Bay 1/GPIO5: U3.10 (GPIO5); also elsewhere on the board
/Main Board/Module Bay 1/GPIO6: U3.11 (GPIO6); also elsewhere on the board
/Main Board/Module Bay 1/GPIO7: U3.12 (GPIO7); also elsewhere on the board
/Main Board/Module Bay 1/GPIO8: U3.13 (GPIO8); also elsewhere on the board
/Main Board/Module Bay 1/GPIO9: U3.14 (GPIO9); also elsewhere on the board
